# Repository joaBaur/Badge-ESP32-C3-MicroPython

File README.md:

# Badge-ESP32-C3-MicroPython

Badge mit ESP32-C3 Super Mini Breakout, OLED 128x64 I2C, 4x Taster und Piezo-Buzzer, programmiert in MicroPython.

## Hardware

Basis-Board: [ESP32-C3 Super Mini](https://prilchen.de/belegungsplan-esp32-c3-supermini/)

| Komponente         | Signal    | ESP32-C3 Pin      |
|---------------------|-----------|--------------------|
| OLED 128x64 (I2C)   | SDA       | GPIO6 (D4)         |
| OLED 128x64 (I2C)   | SCL       | GPIO7 (D5)         |
| OLED 128x64 (I2C)   | VCC       | 3V3                |
| OLED 128x64 (I2C)   | GND       | GND                |
| Taster 1            | Schalter  | GPIO1 (gegen GND)  |
| Taster 2            | Schalter  | GPIO2 (gegen GND)  |
| Taster 3            | Schalter  | GPIO3 (gegen GND)  |
| Taster 4            | Schalter  | GPIO4 (gegen GND)  |
| Piezo-Buzzer (passiv) | Signal  | GPIO0              |
| Piezo-Buzzer (passiv) | GND     | GND                |

Die Taster werden intern per Software-Pullup (`Pin.PULL_UP`) auf High gezogen, ein Taster-Kontakt liegt jeweils gegen GND. Ein gedrückter Taster liest also `0` (Low). Es sind keine externen Pullup-Widerstände nötig. Der Buzzer ist **passiv** und wird per PWM angesteuert (nicht direkt an 3V3/GND anschließen).

## Funktionsweise

Beim Start zeigt das OLED-Display den Text "Hello World" an (zweizeilig, vergrößerte Schrift).

Wird einer der vier Taster gedrückt:

- gibt der passive Buzzer einen Ton in einer der Noten C4, D4, E4 oder F4 aus (262 Hz / 294 Hz / 330 Hz / 349 Hz),
- zeigt das OLED-Display groß die zugehörige Zahl (1, 2, 3 oder 4) an.

Sobald der Taster losgelassen wird, verstummt der Ton und das Display zeigt wieder "Hello World" an. Eine einfache Flankenerkennung mit kurzer Wartezeit dient als Entprellung der Taster.

### Dateien

| Datei         | Beschreibung                                                        |
|---------------|----------------------------------------------------------------------|
| `main.py`     | Hauptprogramm (wird von MicroPython beim Boot automatisch gestartet) |
| `ssd1306.py`  | Treiber für das SSD1306-OLED-Display (I2C/SPI)                       |

## Badge flashen (Code übertragen)

Die Übertragung erfolgt mit [`mpremote`](https://docs.micropython.org/en/latest/reference/mpremote.html). MicroPython muss bereits auf dem ESP32-C3 geflasht sein.

### mpremote installieren

```
python -m pip install --user mpremote
```

### Verbundene Boards anzeigen

```
mpremote connect list
```

### Dateien auf das Board kopieren

Passe `COM5` an den tatsächlichen COM-Port des Boards an (siehe `mpremote connect list` bzw. Geräte-Manager):

```
mpremote connect COM5 cp ssd1306.py :
mpremote connect COM5 cp main.py :
mpremote connect COM5 reset
```

Nach dem Reset startet das Board automatisch `main.py`.

### Live-Ausgabe / REPL

Um die Ausgabe des Boards direkt zu sehen oder eine interaktive REPL zu öffnen:

```
mpremote connect COM5
```

Mit `Strg+]` bzw. `Strg+C` wird die Verbindung/das laufende Programm beendet.

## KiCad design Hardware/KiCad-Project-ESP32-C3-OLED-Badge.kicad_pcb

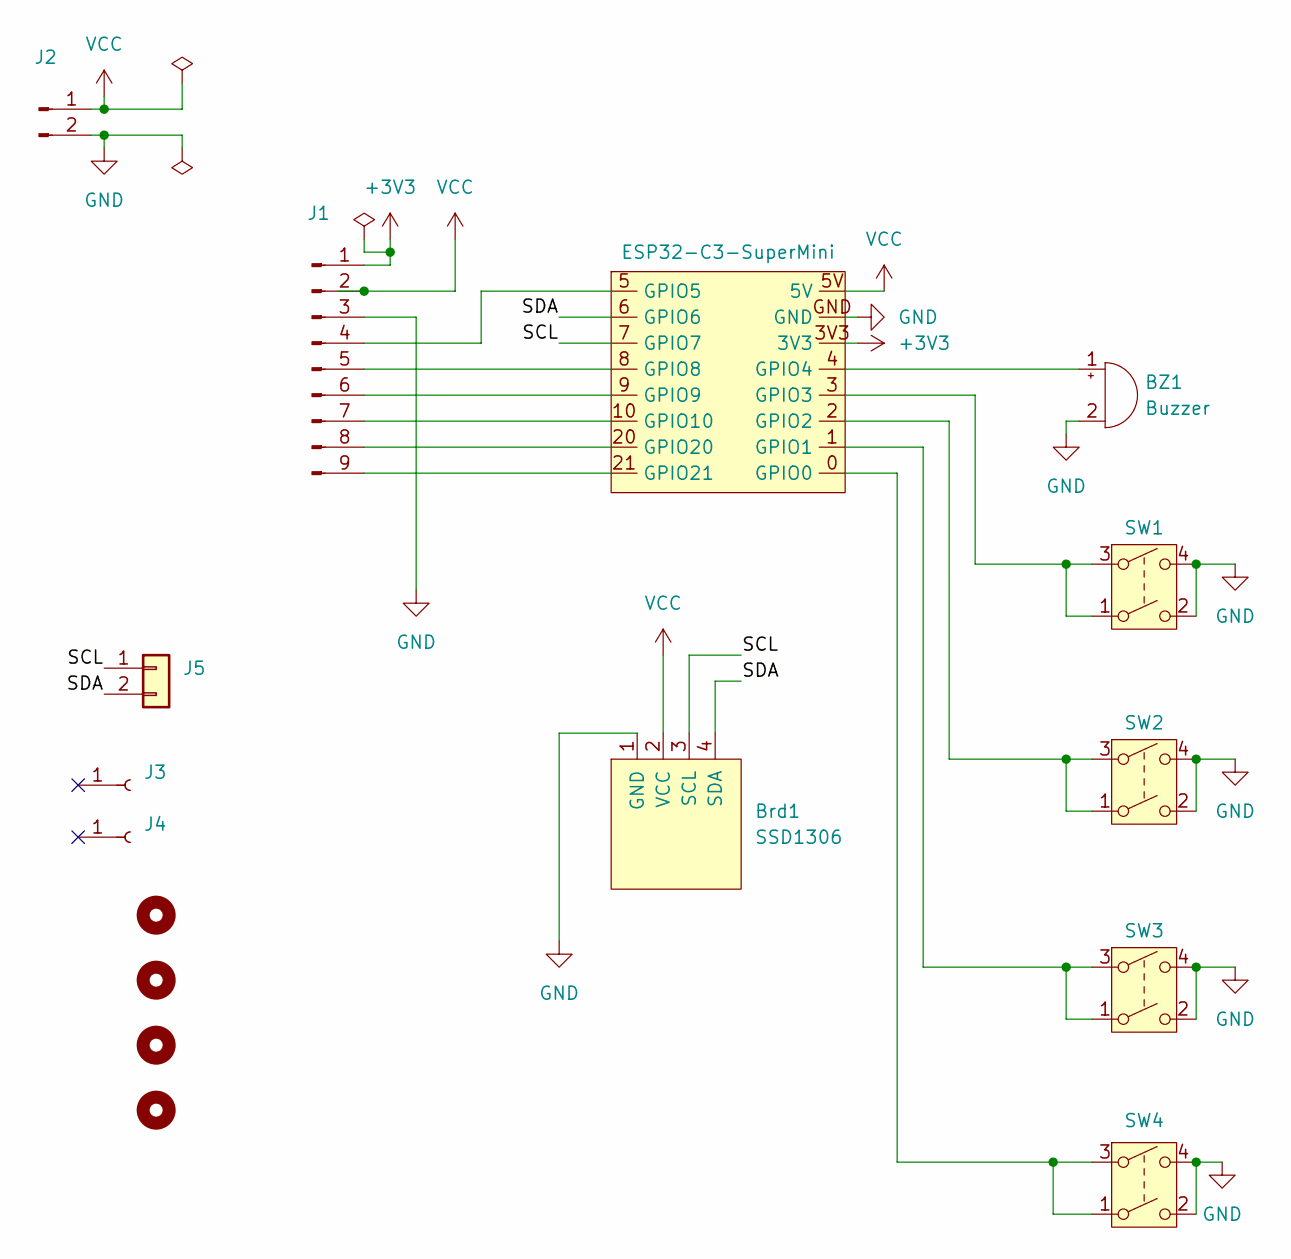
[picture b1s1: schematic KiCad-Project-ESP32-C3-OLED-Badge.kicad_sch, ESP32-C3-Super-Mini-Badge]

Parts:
BZ1: Buzzer; Buzzer_9x4.2RM4
Brd1: SSD1306; 128x64OLED
H1, H2, H3, H4: MountingHole; MountingHole_3.2mm_M3
J1: Conn_01x09_Pin; PinHeader_1x09_P2.54mm_Vertical
J2: Conn_01x02_Pin; PinHeader_1x02_P2.54mm_Vertical
J3, J4: Conn_01x01_Socket; PinHeader_1x01_P2.54mm_Vertical
J5: Conn_01x02; PinHeader_1x02_P2.54mm_Vertical
SW1, SW2, SW3, SW4: SW_DPST; Kurzhubtaster
U1: ESP32-C3-SuperMini

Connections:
+3V3: J1.1, U1.3V3
/SCL: Brd1.3 (SCL), J5.1, U1.7 (GPIO7)
/SDA: Brd1.4 (SDA), J5.2, U1.6 (GPIO6)
GND: BZ1.2 (-), Brd1.1 (GND), J1.3, J2.2, SW1.2, SW1.4, SW2.2, SW2.4, SW3.2, SW3.4, SW4.2, SW4.4, U1.GND
unnamed: BZ1.1 (+), U1.4 (GPIO4)
unnamed: J1.4, U1.5 (GPIO5)
unnamed: J1.5, U1.8 (GPIO8)
unnamed: J1.6, U1.9 (GPIO9)
unnamed: J1.7, U1.10 (GPIO10)
unnamed: J1.8, U1.20 (GPIO20)
unnamed: J1.9, U1.21 (GPIO21)
unnamed: SW4.1, SW4.3, U1.0 (GPIO0)
unnamed: SW3.1, SW3.3, U1.1 (GPIO1)
unnamed: SW2.1, SW2.3, U1.2 (GPIO2)
unnamed: SW1.1, SW1.3, U1.3 (GPIO3)
VCC: Brd1.2 (VCC), J1.2, J2.1, U1.5V

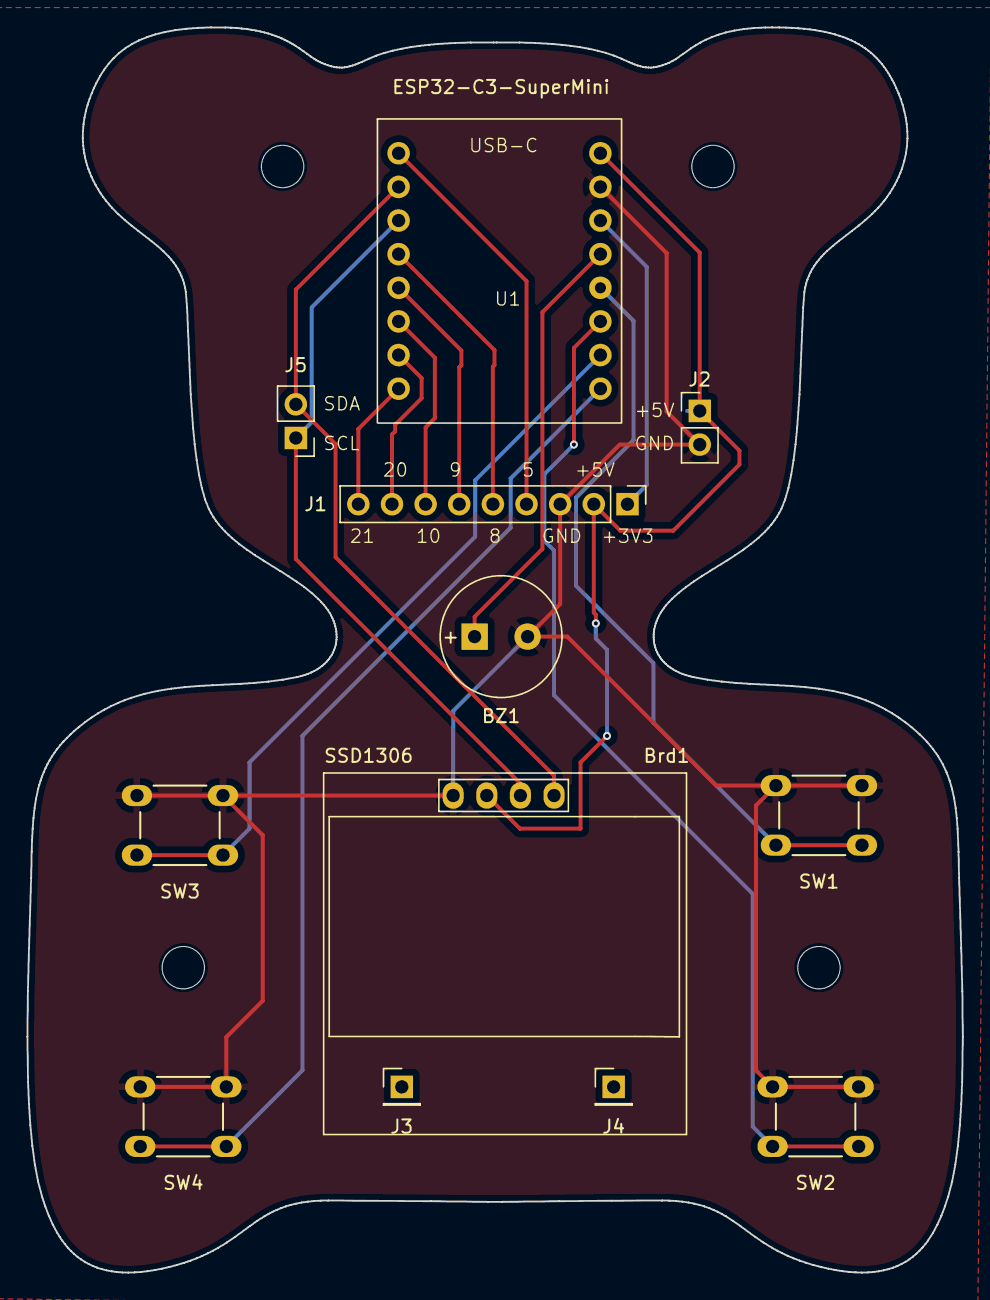
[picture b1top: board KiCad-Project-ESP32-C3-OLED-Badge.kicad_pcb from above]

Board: 2 copper layers, 70.6 x 94.0 mm, 16 parts (0 on the bottom side), 16 nets.
